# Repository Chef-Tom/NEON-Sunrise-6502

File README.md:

# NEON-Sunrise-6502
The 6502 based Prototypes

This started in early 2021 as a work from hom distraction and quickly grew into an obsession.
This repository is to work in conjuction with the blog at http://realcheftom.com/6502
and my YouTube documentation of the project at https://www.youtube.com/watch?v=W5MUhNn74IM&list=PLEm9BpY3woKBx9LlBmEiw2NBphkDs04n8

Comments and updates welcome!

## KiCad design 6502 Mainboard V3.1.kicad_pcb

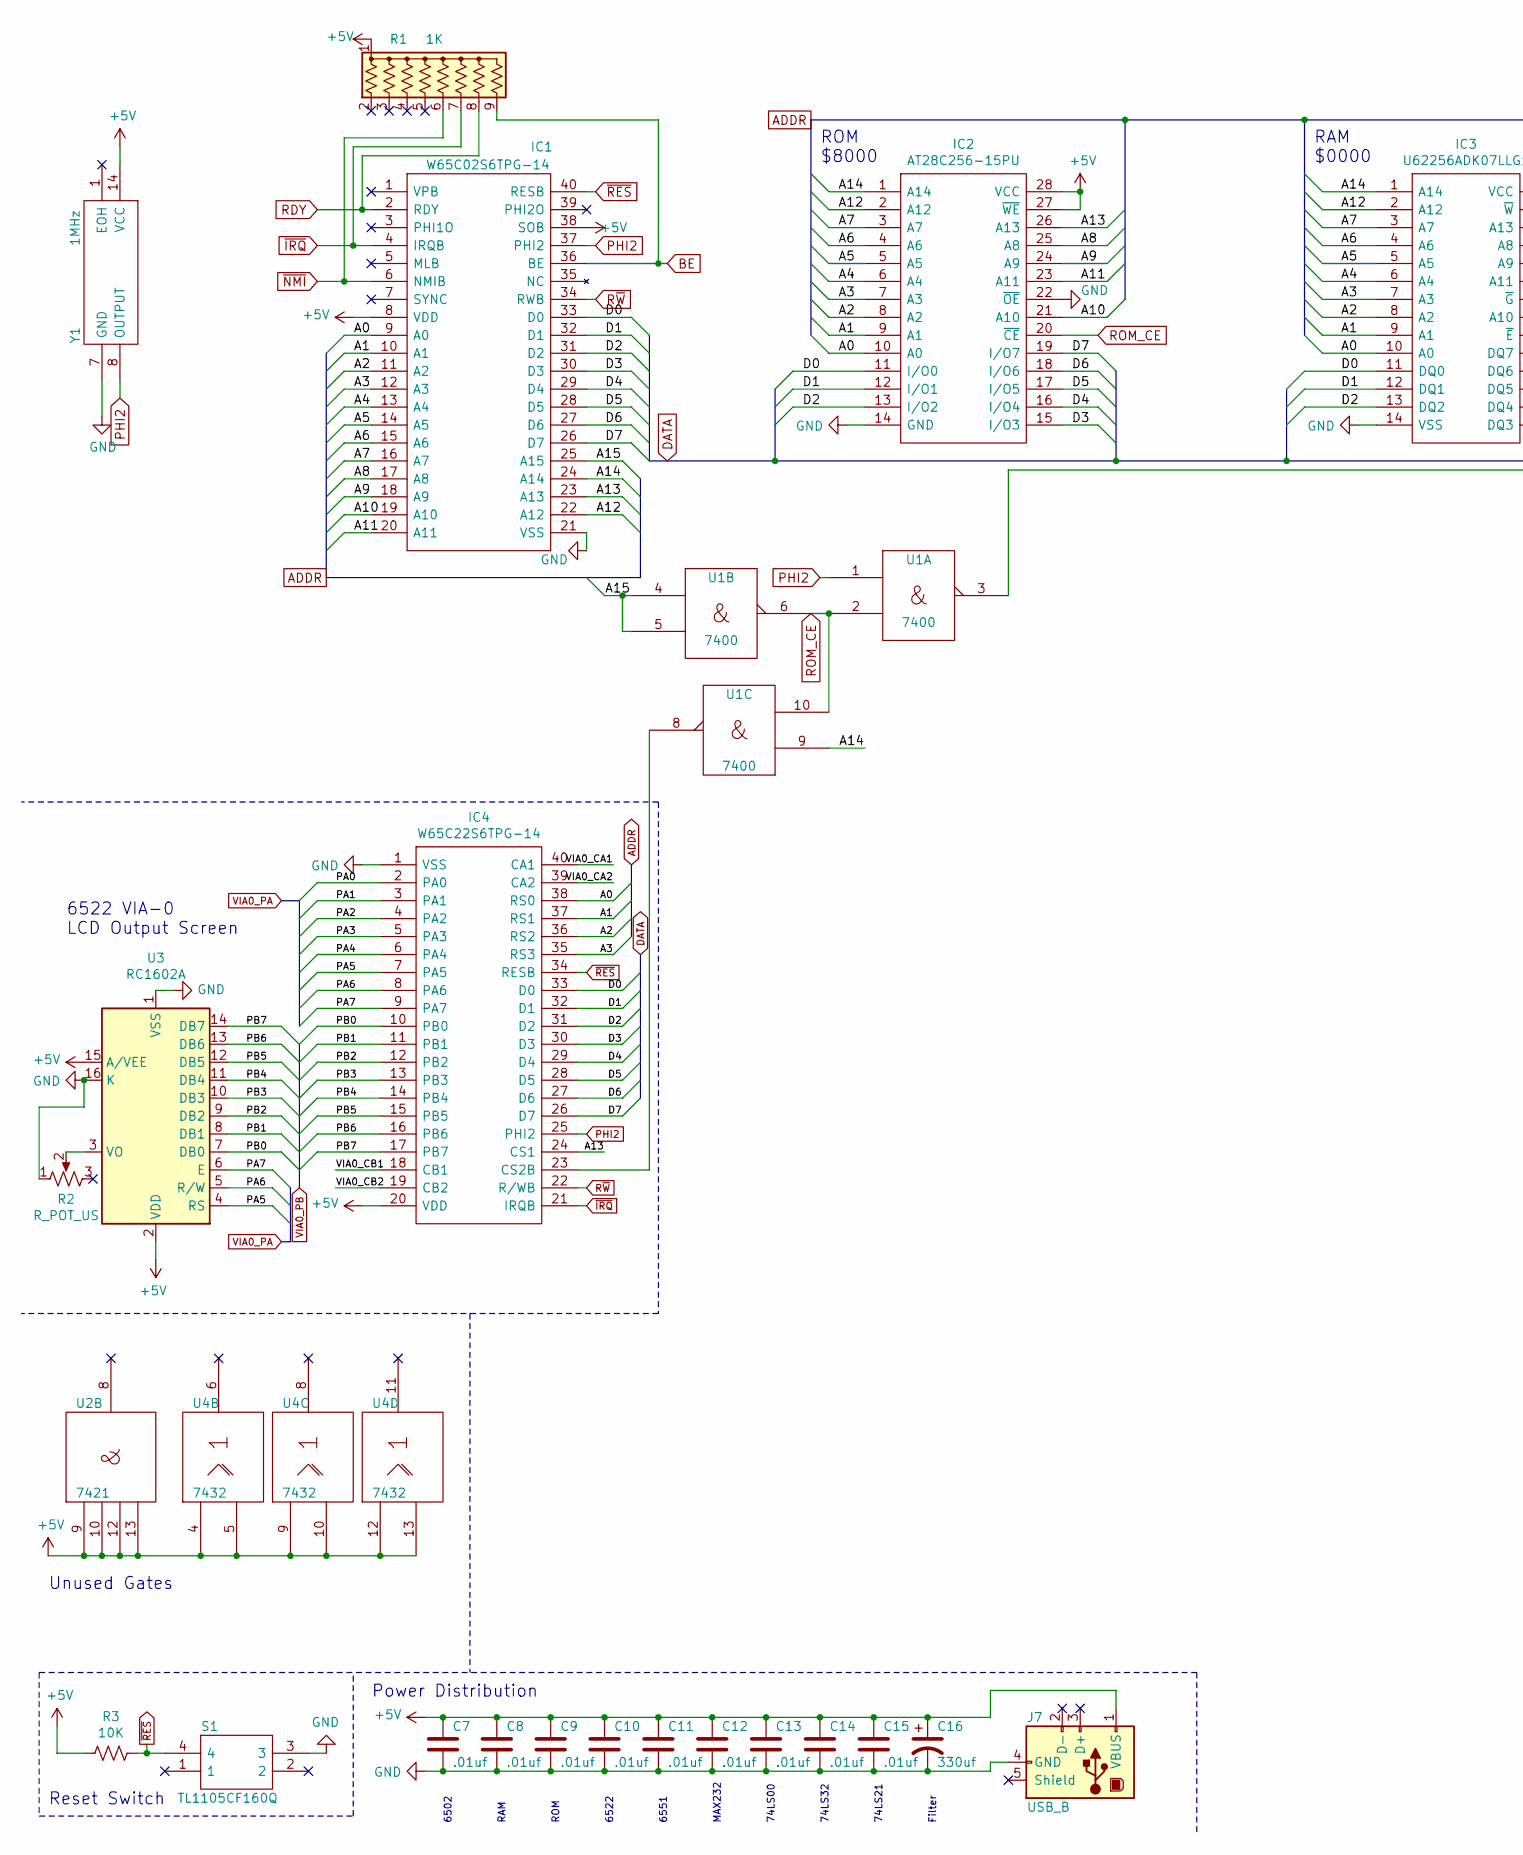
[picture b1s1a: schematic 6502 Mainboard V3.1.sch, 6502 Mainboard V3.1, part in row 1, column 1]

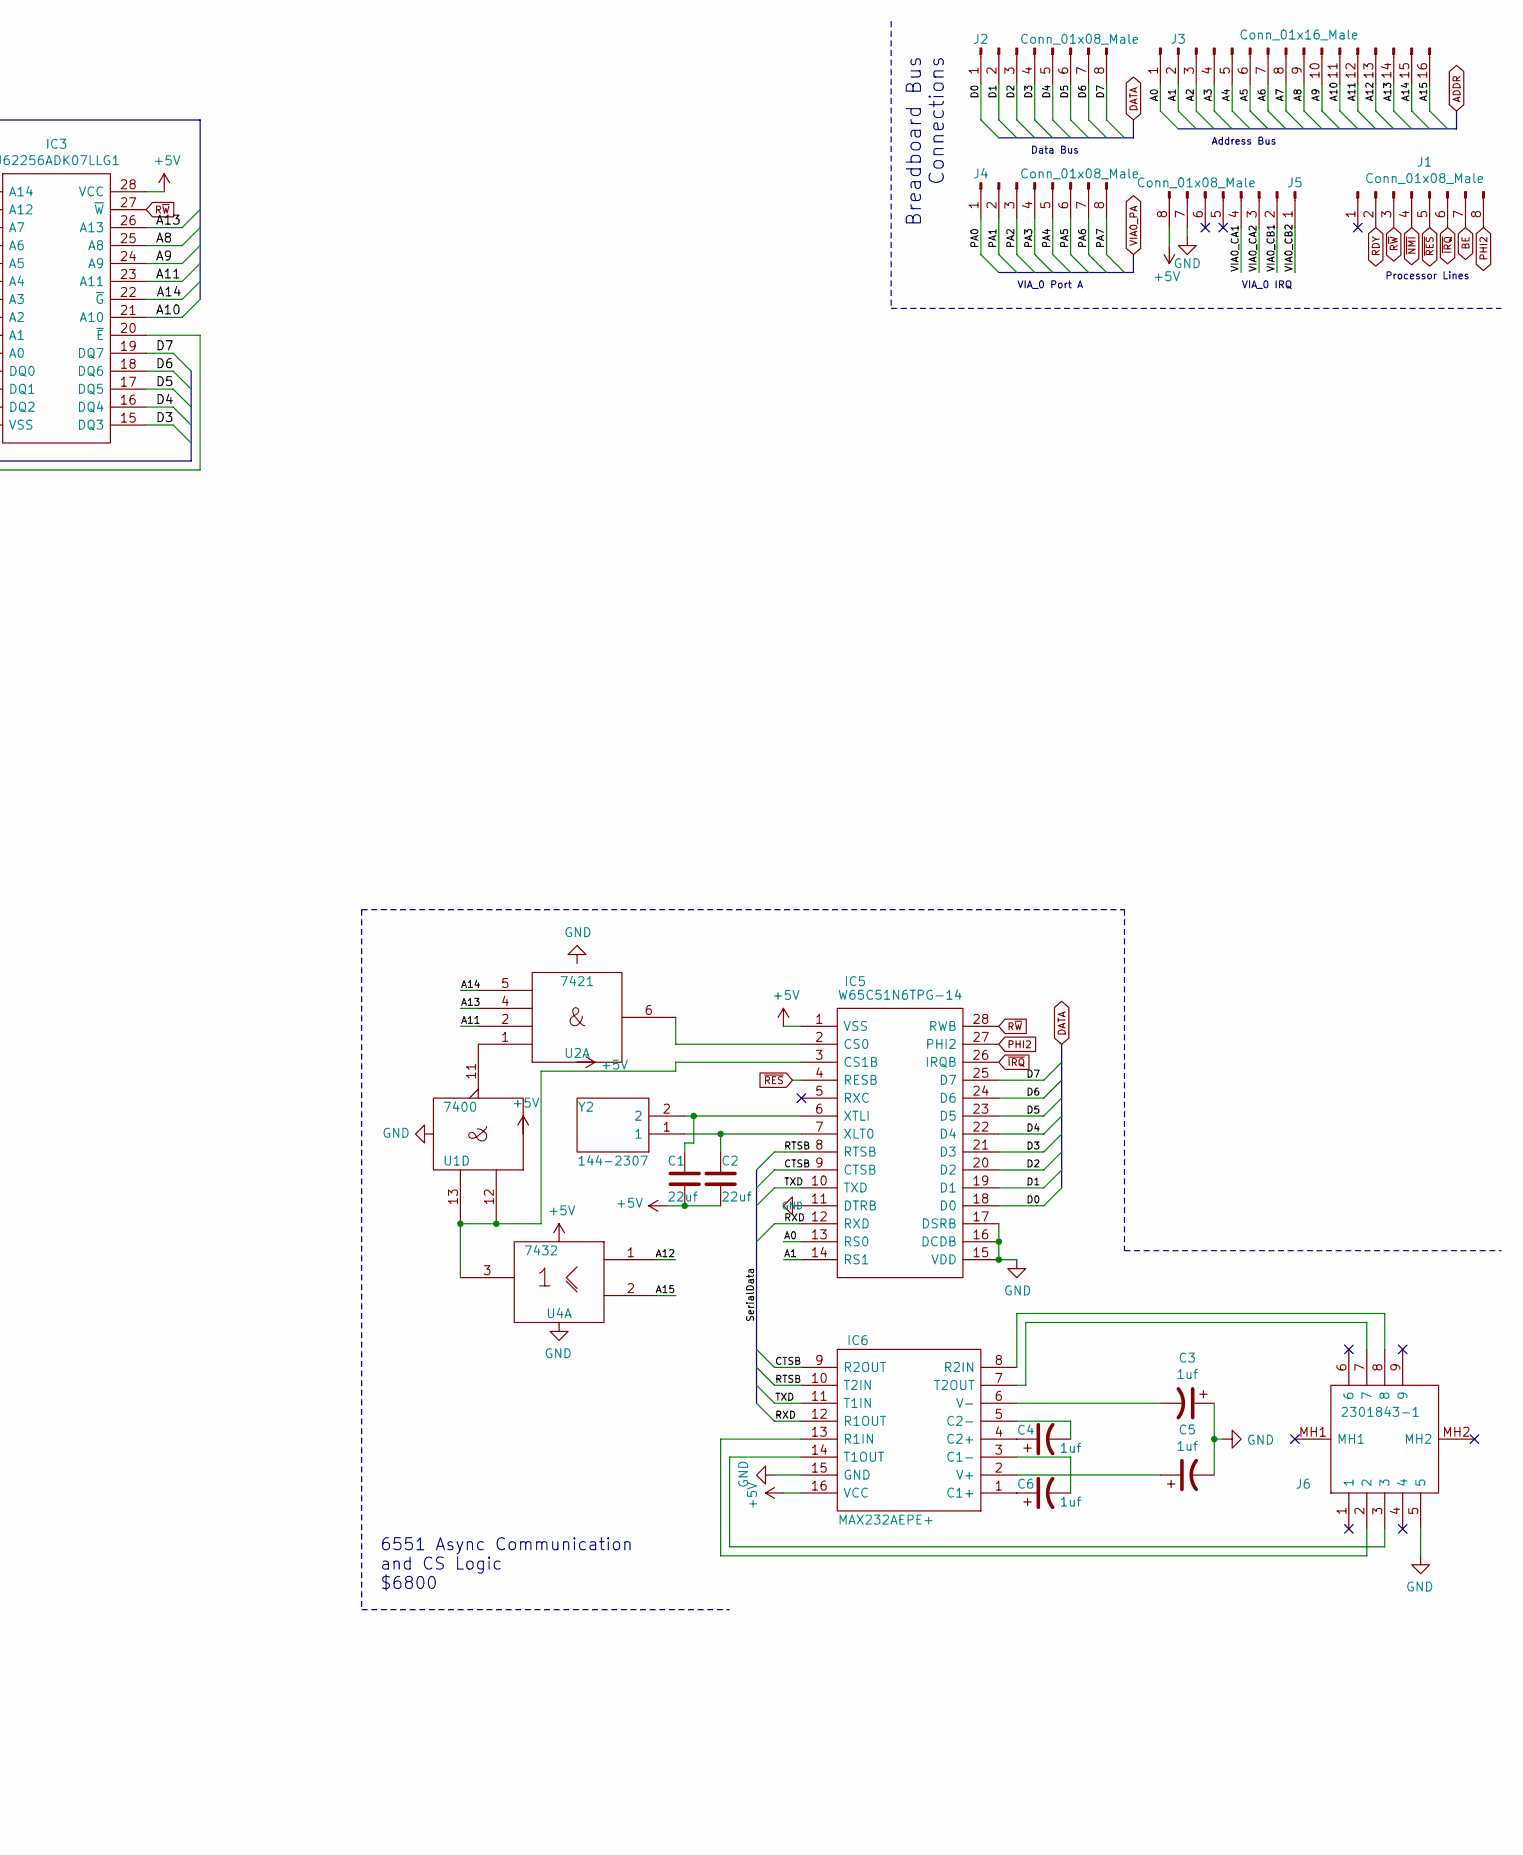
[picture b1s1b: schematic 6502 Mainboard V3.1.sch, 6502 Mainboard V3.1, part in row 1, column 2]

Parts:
C1, C2: 22uf; C_Disc_D3.4mm_W2.1mm_P2.50mm
C3, C4, C5, C6: 1uf; CP_Radial_D5.0mm_P2.50mm
C7, C8, C9, C10, C11, C12, C13, C14, C15: .01uf; C_Disc_D4.3mm_W1.9mm_P5.00mm
C16: 330uf; CP_Radial_D6.3mm_P2.50mm
IC1: W65C02S6TPG-14; DIP-40_W15.24mm_LongPads; Manufacturer_Part_Number W65C02S6TPG-14; Mouser Part Number 955-W65C02S6TPG-14
IC2: AT28C256-15PU; DIP-28_W15.24mm_LongPads; Manufacturer_Part_Number AT28C256-15PU; Mouser Part Number 556-AT28C25615PU
IC3: U62256ADK07LLG1; DIP-28_W15.24mm_LongPads; Manufacturer_Part_Number U62256ADK07LLG1; Mouser Part Number 913-U62256ADK07LLG1
IC4: W65C22S6TPG-14; DIP-40_W15.24mm_LongPads; Manufacturer_Part_Number W65C22S6TPG-14; Mouser Part Number 955-W65C22S6TPG-14
IC5: W65C51N6TPG-14; DIP-28_W15.24mm_LongPads; Manufacturer_Part_Number W65C51N6TPG-14; Mouser Part Number 955-W65C51N6TPG-14
IC6: MAX232AEPE+; DIP-16_W7.62mm_LongPads; Manufacturer_Part_Number MAX232AEPE+; Mouser Part Number 700-MAX232AEPE
J1, J2, J4, J5: Conn_01x08_Male; PinHeader_1x08_P2.54mm_Vertical
J3: Conn_01x16_Male; PinHeader_1x16_P2.54mm_Vertical
J6: 2301843-1; 23018431; Manufacturer_Part_Number 2301843-1; Mouser Part Number 571-2301843-1
J7: USB_B; USB_B_Lumberg_2411_02_Horizontal
R1: 1K; R_Array_SIP9
R2: R_POT_US; Potentiometer_Vishay_T73YP_Vertical
R3: 10K; R_Axial_DIN0411_L9.9mm_D3.6mm_P15.24mm_Horizontal
S1: TL1105CF160Q; Manufacturer_Part_Number TL1105CF160Q; Mouser Part Number 612-TL1105C
U1: 7400; DIP-14_W7.62mm_LongPads
U2: 7421; DIP-14_W7.62mm_LongPads
U3: RC1602A; WC1602A
U4: 7432; DIP-14_W7.62mm_LongPads
Y1: 1MHz; MXO45T2C1M0000; Manufacturer_Part_Number MXO45T-2C-1M0000; Mouser Part Number 774-MXO45T-2C-1M0000
Y2: 144-2307; Crystal_HC52-6mm_Vertical; Manufacturer_Part_Number 144-2307

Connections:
+5V: C1.2, C2.2, C7.1, C8.1, C9.1, C10.1, C11.1, C12.1, C13.1, C14.1, C15.1, C16.1, IC1.8 (VDD), IC1.38 (SOB), IC2.27 (~WE), IC2.28 (VCC), IC3.28 (VCC), IC4.20 (VDD), IC5.1 (VSS), IC6.16 (VCC), J5.8, J7.1 (VBUS), R1.1 (common), R3.2, U1.14 (Vcc), U2.9, U2.10, U2.12, U2.13, U2.14 (Vcc), U3.2 (VDD), U3.15 (A/VEE), U4.4, U4.5, U4.9, U4.10, U4.12, U4.13, U4.14 (Vcc), Y1.14 (VCC)
/A0: IC1.9 (A0), IC2.10 (A0), IC3.10 (A0), IC4.38 (RS0), IC5.13 (RS0), J3.1
/A1: IC1.10 (A1), IC2.9 (A1), IC3.9 (A1), IC4.37 (RS1), IC5.14 (RS1), J3.2
/A2: IC1.11 (A2), IC2.8 (A2), IC3.8 (A2), IC4.36 (RS2), J3.3
/A3: IC1.12 (A3), IC2.7 (A3), IC3.7 (A3), IC4.35 (RS3), J3.4
/A4: IC1.13 (A4), IC2.6 (A4), IC3.6 (A4), J3.5
/A5: IC1.14 (A5), IC2.5 (A5), IC3.5 (A5), J3.6
/A6: IC1.15 (A6), IC2.4 (A6), IC3.4 (A6), J3.7
/A7: IC1.16 (A7), IC2.3 (A7), IC3.3 (A7), J3.8
/A8: IC1.17 (A8), IC2.25 (A8), IC3.25 (A8), J3.9
/A9: IC1.18 (A9), IC2.24 (A9), IC3.24 (A9), J3.10
/A10: IC1.19 (A10), IC2.21 (A10), IC3.21 (A10), J3.11
/A11: IC1.20 (A11), IC2.23 (A11), IC3.23 (A11), J3.12, U2.2
/A12: IC1.22 (A12), IC2.2 (A12), IC3.2 (A12), J3.13, U4.1
/A13: IC1.23 (A13), IC2.26 (A13), IC3.26 (A13), IC4.24 (CS1), J3.14, U2.4
/A14: IC1.24 (A14), IC2.1 (A14), IC3.1 (A14), IC3.22 (~G), J3.15, U1.9, U2.5
/A15: IC1.25 (A15), J3.16, U1.4, U1.5, U4.2
/CTSB: IC5.9 (CTSB), IC6.9 (R2OUT)
/D0: IC1.33 (D0), IC2.11 (I/O0), IC3.11 (DQ0), IC4.33 (D0), IC5.18 (D0), J2.1
/D1: IC1.32 (D1), IC2.12 (I/O1), IC3.12 (DQ1), IC4.32 (D1), IC5.19 (D1), J2.2
/D2: IC1.31 (D2), IC2.13 (I/O2), IC3.13 (DQ2), IC4.31 (D2), IC5.20 (D2), J2.3
/D3: IC1.30 (D3), IC2.15 (I/O3), IC3.15 (DQ3), IC4.30 (D3), IC5.21 (D3), J2.4
/D4: IC1.29 (D4), IC2.16 (I/O4), IC3.16 (DQ4), IC4.29 (D4), IC5.22 (D4), J2.5
/D5: IC1.28 (D5), IC2.17 (I/O5), IC3.17 (DQ5), IC4.28 (D5), IC5.23 (D5), J2.6
/D6: IC1.27 (D6), IC2.18 (I/O6), IC3.18 (DQ6), IC4.27 (D6), IC5.24 (D6), J2.7
/D7: IC1.26 (D7), IC2.19 (I/O7), IC3.19 (DQ7), IC4.26 (D7), IC5.25 (D7), J2.8
/PA0: IC4.2 (PA0), J4.1
/PA1: IC4.3 (PA1), J4.2
/PA2: IC4.4 (PA2), J4.3
/PA3: IC4.5 (PA3), J4.4
/PA4: IC4.6 (PA4), J4.5
/PA5: IC4.7 (PA5), J4.6, U3.4 (RS)
/PA6: IC4.8 (PA6), J4.7, U3.5 (R/W)
/PA7: IC4.9 (PA7), J4.8, U3.6 (E)
/PB0: IC4.10 (PB0), U3.7 (DB0)
/PB1: IC4.11 (PB1), U3.8 (DB1)
/PB2: IC4.12 (PB2), U3.9 (DB2)
/PB3: IC4.13 (PB3), U3.10 (DB3)
/PB4: IC4.14 (PB4), U3.11 (DB4)
/PB5: IC4.15 (PB5), U3.12 (DB5)
/PB6: IC4.16 (PB6), U3.13 (DB6)
/PB7: IC4.17 (PB7), U3.14 (DB7)
/RTSB: IC5.8 (RTSB), IC6.10 (T2IN)
/RXD: IC5.12 (RXD), IC6.12 (R1OUT)
/TXD: IC5.10 (TXD), IC6.11 (T1IN)
/VIA0_CA1: IC4.40 (CA1), J5.4
/VIA0_CA2: IC4.39 (CA2), J5.3
/VIA0_CB1: IC4.18 (CB1), J5.2
/VIA0_CB2: IC4.19 (CB2), J5.1
BE: IC1.36 (BE), J1.7, R1.9 (R8)
GND: C3.1, C5.2, C7.2, C8.2, C9.2, C10.2, C11.2, C12.2, C13.2, C14.2, C15.2, C16.2, IC1.21 (VSS), IC2.14 (GND), IC2.22 (~OE), IC3.14 (VSS), IC4.1 (VSS), IC5.11 (DTRB), IC5.15 (VDD), IC5.16 (DCDB), IC5.17 (DSRB), IC6.15 (GND), J5.7, J6.5, J7.4 (GND), R2.1, S1.3, U1.7 (GND), U2.7 (Gnd), U3.1 (VSS), U3.16 (K), U4.7 (Gnd), Y1.7 (GND)
unnamed: C1.1, IC5.6 (XTLI), Y2.2
unnamed: C2.1, IC5.7 (XLT0), Y2.1
unnamed: C3.2, IC6.6 (V-)
unnamed: C4.1, IC6.4 (C2+)
unnamed: C4.2, IC6.5 (C2-)
unnamed: C5.1, IC6.2 (V+)
unnamed: C6.1, IC6.1 (C1+)
unnamed: C6.2, IC6.3 (C1-)
unnamed: IC3.20 (~E), U1.3
unnamed: IC4.23 (CS2B), U1.8
unnamed: IC5.2 (CS0), U2.6
unnamed: IC5.3 (CS1B), U1.12, U1.13, U4.3
unnamed: IC6.7 (T2OUT), J6.7
unnamed: IC6.8 (R2IN), J6.8
unnamed: IC6.13 (R1IN), J6.2
unnamed: IC6.14 (T1OUT), J6.3
unnamed: R2.2, U3.3 (VO)
unnamed: U1.11, U2.1
PHI2: IC1.37 (PHI2), IC4.25 (PHI2), IC5.27 (PHI2), J1.8, U1.1, Y1.8 (OUTPUT)
RDY: IC1.2 (RDY), J1.2, R1.8 (R7)
ROM_CE: IC2.20 (~CE), U1.2, U1.6, U1.10
R~W: IC1.34 (RWB), IC3.27 (~W), IC4.22 (R/WB), IC5.28 (RWB), J1.3
~IRQ: IC1.4 (IRQB), IC4.21 (IRQB), IC5.26 (IRQB), J1.6, R1.7 (R6)
~NMI: IC1.6 (NMIB), J1.4, R1.6 (R5)
~RES: IC1.40 (RESB), IC4.34 (RESB), IC5.4 (RESB), J1.5, R3.1, S1.4

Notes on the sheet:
Reset Switch
6551 Async Communication and CS Logic $6800
ROM $8000
RAM $0000
6522 VIA-0 LCD Output Screen
6502
RAM
ROM
6522
6551
MAX232
74LS00
74LS32
74LS21
Filter
Power Distribution
Unused Gates
VIA_0 IRQ
VIA_0 Port A
Processor Lines
Address Bus
Data Bus
Breadboard Bus Connections

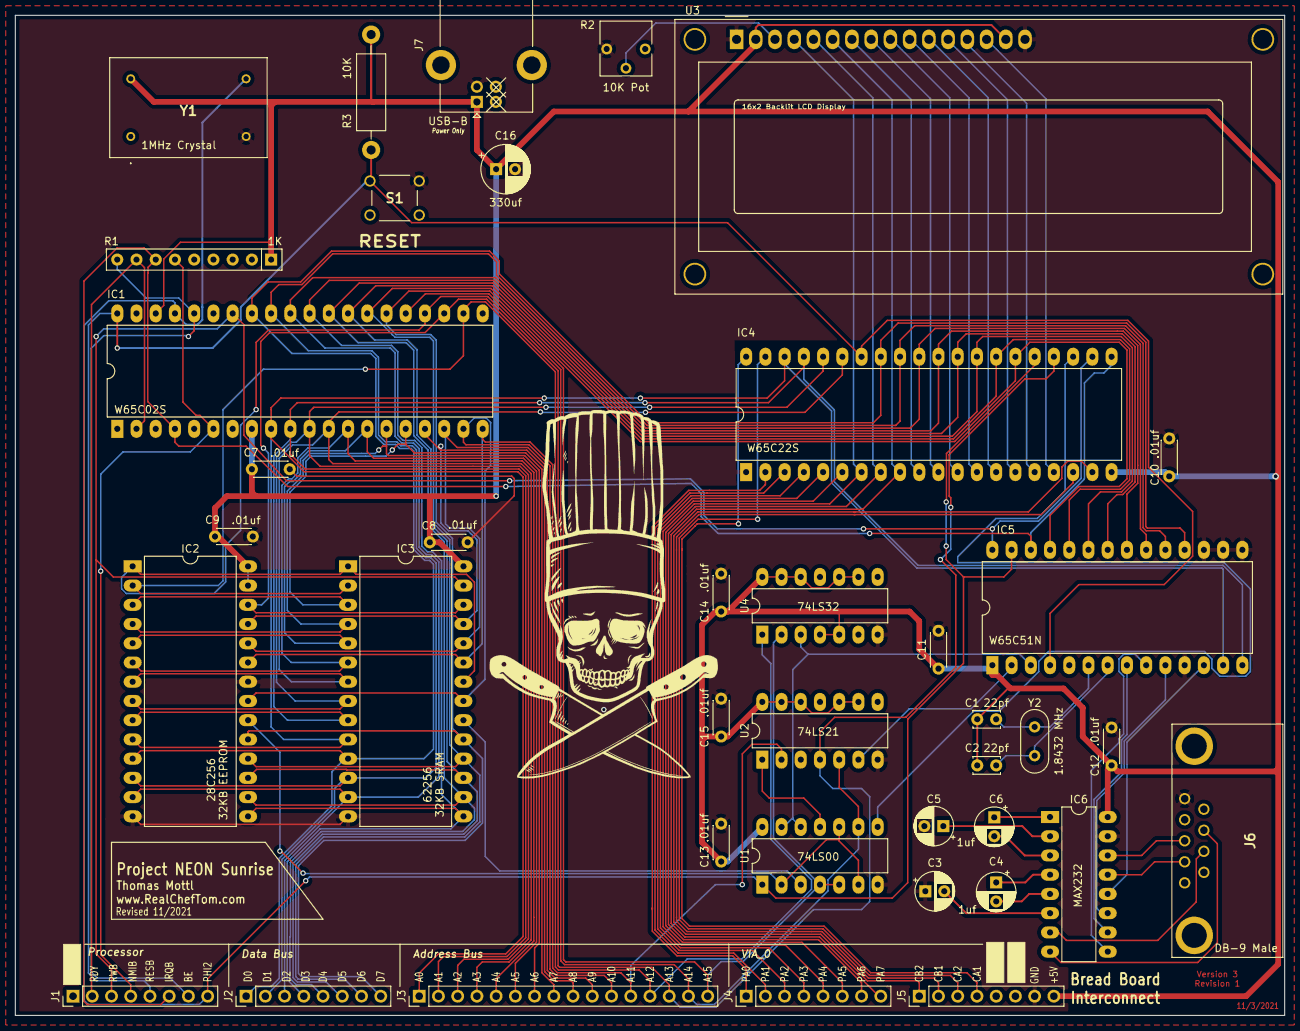
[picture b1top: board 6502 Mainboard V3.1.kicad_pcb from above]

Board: 2 copper layers, 167.6 x 132.1 mm, 39 parts (0 on the bottom side), 76 nets.

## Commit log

2021-09-26 Add files via upload
    Initial upload using the V0.2 mainboard files and the four button interrupt test.
2022-01-17 Add files via upload
    After fixing the bus contention that arose from the ACIA addresses being a subset of the VIA addresses and not disabling the VIA, So that was fun.
